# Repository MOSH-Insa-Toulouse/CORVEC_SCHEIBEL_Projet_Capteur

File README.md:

# CORVEC_SCHEIBEL_Projet_Capteur

[Lien GitHub du projet ](https://github.com/MOSH-Insa-Toulouse/CORVEC_SCHEIBEL_Projet_Capteur)

Étudiantes en 4ème année Génie Physique à l’INSA (Institut National des Sciences Appliquées) de Toulouse ce ReadMe présente le projet réalisé dans le cadre de l’UF « Du capteur au banc de test ». L’objectif de ce projet est de designer et construire un PCB Shield incluant un capteur de déformation en graphite couplé à un circuit analogique. Un code Arduino permet de contrôler le tout et de communiquer les mesures du capteur vers une application Android.

## Sommaire 

- [1. Contexte du projet](#1-contexte-du-projet)  

- [2. Fabrication du capteur](#2-fabrication-du-capteur)  
    - [a. Kicad](#a-kicad)
    - [b. Réalisation du PCB](#b-réalisation-du-pcb)
- [3. Contrôle et interface du capteur](#3-contrôle-et-interface-du-capteur)
- [a. Code Arduino](#a-code-arduino)
- [b. Application Android](#b-application-android)
- [4. Banc de test](#4-banc-de-test)
- [5. Pistes d'amélioration](#5-pistes-damélioration)
- [6. Commentaires et conclusion](#6-commentaires-et-conclusion)

## 1. Contexte du projet

Le crayon papier est un objet du quotidien et fait partie intégrante de nos vies depuis bien longtemps. La mine d’un crayon est composée d'une fine poudre de graphite liées par des argiles. Lorsque l’on effectue des traces de crayons sur une feuille de papier (surface naturellement poreuse), des particules ultrafines de graphite se déplosent en surface. Ces traces sont des films minces conducteurs constituées de réseaux percolés. Elles peuvent ainsi jouer le rôle de conducteur passif dans divers dispositifs et peuvent être également utilisées en tant que conducteur actif dans des capteurs piézorésistifs. En 2014, les chercheurs Cheng-Wei Lin, Zhibo Zhao, Jaemyung Kim & Jiaxing Huang ont publié l’article « Pencil Drawn Strain Gauges and Chemiresistors on Paper » dans lequel ils démontrent que « les traces de crayon peuvent fonctionner non seulement comme des jauges de contrainte pour détecter les déflexions de compression et de traction, mais également comme des résistances chimiques sensibles aux vapeurs chimiques volatiles »[1]. 

Pour rappels : Les crayons en graphite sont désignés comme ceci :

- 9H à H (avec H9 le plus dur et léger)
- HB
- 9B à B (avec 9B le plus doux et sombre)

Les résultats présentés par l’équipe de chercheurs sont les suivants : les résistances mesurées sans contrainte pour des mines 9B, 6B, 2B, and HB sont respectivement de 200 kΩ, 500 kΩ, 2MΩ, 20 MΩ. Plus les mines sont douces et sombres (donc contenant plus de graphite) plus la résistance est faible.  
L’étude des chercheurs a révélé que les traces laissées par des crayons de duretés supérieures et égales à 2H ne pouvaient être mesurées, elles étaient donc non conductrices. Cependant les traces de crayons HB ont montré la plus grande réponse, elles se situeraient à priori juste au-dessus du seuil de percolation. Les mesures ont été réalisés via un programme Labview avec un compteur source Keithley 2400 d’une valeur de 5760€.  

À travers ce projet nous avons cherché à mesurer la valeur de résistance 2H et ce, avec un dispositif bas coût et facilement transportable.

## 2. Fabrication du capteur

Le capteur de déformation en graphite est une jauge de contrainte. Le principe consiste ici appliquer des forces de compression ou de traction sur une feuille de papier où a été déposé du graphite via un crayon papier (Figure 1).  Comme énoncé précédemment, les traces laissées par le crayon vont, sous compression ou traction, présenter une variation de résistance. Suite à cette faible variation, on mesure une tension, grâce à un circuit d'amplification transimpédance.

Figure 1

### a. Kicad

La schématique du circuit a été créé via le logiciel LTSpice IV (Figures 2). La schématique présente une partie lecture analogique, nous utilisons un amplificateur trans-impédance. Il s’agit d’un convertisseur courant-tension permettant d’amplifier la sortie de courant du capteur.  Ce circuit trans-impédance à filtre passe-bas nous permet de récupérer les données du capteur de traction (pour plus de détails : voir notre datasheet, partie « Exemple d’intégration »). Une autre partie expose les modules pouvant être ajoutés sur la carte : un écran OLED, un Bluetooth et un encodeur rotatoire.  Après avoir généré la liste des empreintes des composants, nous avons pu concevoir notre PCB Shield grâce au logiciel KICAD (Figures 3).

Figures 2

Figures 3

### b. Réalisation du PCB

Le masque de notre PCB a ensuite été imprimé et placé sur une plaque recouverte d’une résine. La résine non protégée par le masque est exposée aux UV. Une solution basique attaque les dépôts de résine insolée pour révéler certaines zones du PCB. La plaque est ensuite chauffée dans une solution afin d'attaquer les zones de cuivre non désirées. Le PCB est ensuite percé et les différents composants y sont soudés (Figures 4).

Figures 4

## 3. Contrôle et interface du capteur

### a. Code Arduino

Le PCB se plug sur une carte Arduino (Figure 5). Le branchement est détaillé dans la datasheet. Le code Arduino ([lien code](/Arduino_code/Arduino_capteur_graphite.ino)) permet de :

- Lire la tension (ADC) délivrée par le capteur (capteur graphite + circuit amplificateur)
- D'envoyer la donnée vers l'application Android via la connection Blueotooth établie
- De calculer la resistance du capteur graphite équivalente à cette tension pour l'afficher sur l'écran OLED

Figure 5

### b. Application Android

L'application Android affiche la valeur de la tension lue par l'ensemble du capteur. Elle calcule la valeur de la résistance en (Ohm) et l'affiche au dessus de la tension. Parallèlement un graphique montre la valeur de la résistance en fonction du temps.
L'îcone "Bluetooth" permet d'ouvrir la liste des appareils associés au smartphone pour établir la connexion Bluetooth avec le capteur.

Cette application a été créée sur le site [MIT app inventor](https://appinventor.mit.edu/). Pour télécharger notre application, il faut ouvrir cette [apk](/Application_Android/Capteur.apk) depuis un smartphone.

## 4. Banc de test

Une fois le branchement du capteur effectué nous réalisons les mesures de caractérisation. Nous utilisons une pièce imprimée en 3D(Figure 6). Elle comporte 7 rayons différents, cela permet d’appliquer plusieurs contraintes connues à notre capteur. Pour nos mesures les diamètres notés R1 à R6 sont utilisés.

- ETAPE 1 : Dépôt du graphite à tester sur la feuille de papier, en coloriant.
- ETAPE 2 : Lecture de la valeur de l’offset, notée R0 grâce à l’écran OLED ou via l’application.
- ETAPE 3 : Application de la première contrainte au rayon R1 et lecture de la résistance R du capteur.
- ETAPE 4 : Calcul de ∆R.
- ETAPE 5 : Répétition des étapes 2, 3 et 4 jusqu’au rayon R6.
- ETAPE 6 : Calcul de la déformation appliquée pour chaque rayon.
- ETAPE 7 : Affichage de (∆R )/R en fonction de la déformation.

Figure 6

## 5. Pistes d'améliorations

Les différentes mesures effectuées ne sont pas répétables. Dès la première mesure du protocole de test, le capteur entre dans le domaine de non-détérioration, c’est-à-dire que ses caractéristiques métrologiques sont modifiées. En effet la résistance d'offset varie après chaque nouvelle contrainte appliquée, ce qui influe sur le résultat, d’où l’importance de relever avant chaque mesure la nouvelle valeur de R0. À partir des rayons R3 ou R4 nous entrons dans le domaine de non-destruction du capteur, les caractéristiques métrologiques sont modifiées de façon irréversible. L’offset devient de plus en plus important et il n’est plus possible de répéter les précédentes mesures sans entacher les résultats d’erreurs. Il est plutôt conseillé de changer de capteur, en effet lorsqu’une contrainte trop élevée est appliquée, les réseaux percolés sur graphite ne peuvent revenir à leur état d’origine.

Plusieurs pistes d’améliorations sont envisageables, sur différents éléments du capteur :

**Concernant la précision des mesures** du banc de test : les mesures effectuées sont peu répétables. En effet, entre chaque série de mesures les déformations appliquées peuvent varier (le banc de test ne permettant pas d’appliquer une déformation identique) tout comme la  concentration de graphite déposée sur le papier (manque de précision du coloriage).

Pour diminuer l’erreur sur les mesures, nous pourrions répéter les tests sur un grand nombre de capteurs équivalents et pour chaque contrainte, nous aurions ainsi une moyenne arithmétique de la valeur de résistance.

Un autre moyen d’améliorer la répétabilité des mesures, serait de fabriquer un banc de test plus précis et fiable, par exemple l’utilisation d’un banc de test contrôlé par un cervo moteur permettrait d’appliquer une contrainte beaucoup plus précise et répétable que la contrainte appliquée à la main sur la pièce 3D.

Concernant le **PCB** : Pour adapter les mesures des résistances en fonction des types de capteur (donc en fonction des différents types de graphite), il serait très utile de pouvoir modifier le gain de l’amplificateur transimpédance. Le gain est influencé par le rapport R2/R3, R3 est important pour le filtrage, c’est donc la résistance R2 qui permet de jouer sur le gain. Plutôt que de souder une résistance d’une valeur fixe, il serait alors judicieux de souder des plots. Ainsi le changement de R2 serait plus facile.

Enfin le **code Arduino** pourrait également être développé. Si des plots sont soudés sur le PCB pour pouvoir changer la résistance R2, alors l’Arduino pourrait gérer un encodeur rotatoire. Celui-ci permettrait de modifier la valeur de R2 dans le code, et ainsi faire le lien entre la résistance physique et la valeur de R2 dans les formules du code. Le code Arduino peut toujours être amélioré, d’autres fonctionnalités sont possibles, comme par exemple l’affichage d’un menu sur l’écran OLED. Ce menu permettrait d’entrer une nouvelle valeur de R2, de modifier la valeur de l’offset du capteur ou encore de changer la vitesse de transfert des données entre le capteur et l’application, etc…

## 6. Commentaires et conclusion

Les résultats des mesures effectuées sont disponibles dans notre datasheet. Nous pouvons apporter les commentaires suivants : plus une mine est douce, plus elle est concentrée en carbone et moins la variation de résistance est importante. En effet les réseaux percolés sont beaucoup plus denses et on a une meilleure conduction. Lorsqu’on applique une contrainte sur ce type de mine, les réseaux percolés, du fait de leur nombre, sont peu impactés. Ce qui pourrait expliquer pourquoi la mine la plus concentrée 6B a montré une variation de résistance quasiment constante. Les graphites 3B et B varient le plus linéairement. L'application d'une traction vient déconnecter les réseaux, on a une diminution de la conductivité. Les mines plus dures comme HB ou 2H creusent davantage le papier mais sont moins concentrées en carbone. Les mesures effectuées présentaient de très fortes variations de résistances et ces dernières étaient très instables, donc plus difficile à mesurer notamment le 2H. Cependant, malgré les grandes incertitudes sur ces mesures nous avons tout de même observé des variations de résistance sur le 2H contrairement aux chercheurs cités précédemment. Donc, la concentration en graphite du type 2H se situe probablement au-dessus du seuil de percolation.

Il est surprenant de réaliser un capteur de déformation avec si peu de matériel, une simple feuille de papier coloriée au crayon permet de mettre en évidence de faibles déformations. Cependant on notera que le capteur en graphite est très peu précis et relativement fragile, sans oublier qu’il manque fortement de répétabilité. Cet inconvénient est problématique pour un capteur, car il ne permet pas d'accéder de manière fiable à des valeurs de contraintes inconnues.
L’élaboration de ce capteur en graphite a permis de nous rendre compte de l’importance de certaines caractéristiques des capteurs. Ce projet nous a aussi fait découvrir l’Arduino, qui est très pratique par sa polyvalence et ses multiples applications.

Références :

[1] Lin, C.-W., Zhao, Z., Kim, J. & Huang, J. Pencil Drawn Strain
Gauges and Chemiresistors on Paper. Sci. Rep. 4, 3812; DOI:10.1038/srep03812 (2014)

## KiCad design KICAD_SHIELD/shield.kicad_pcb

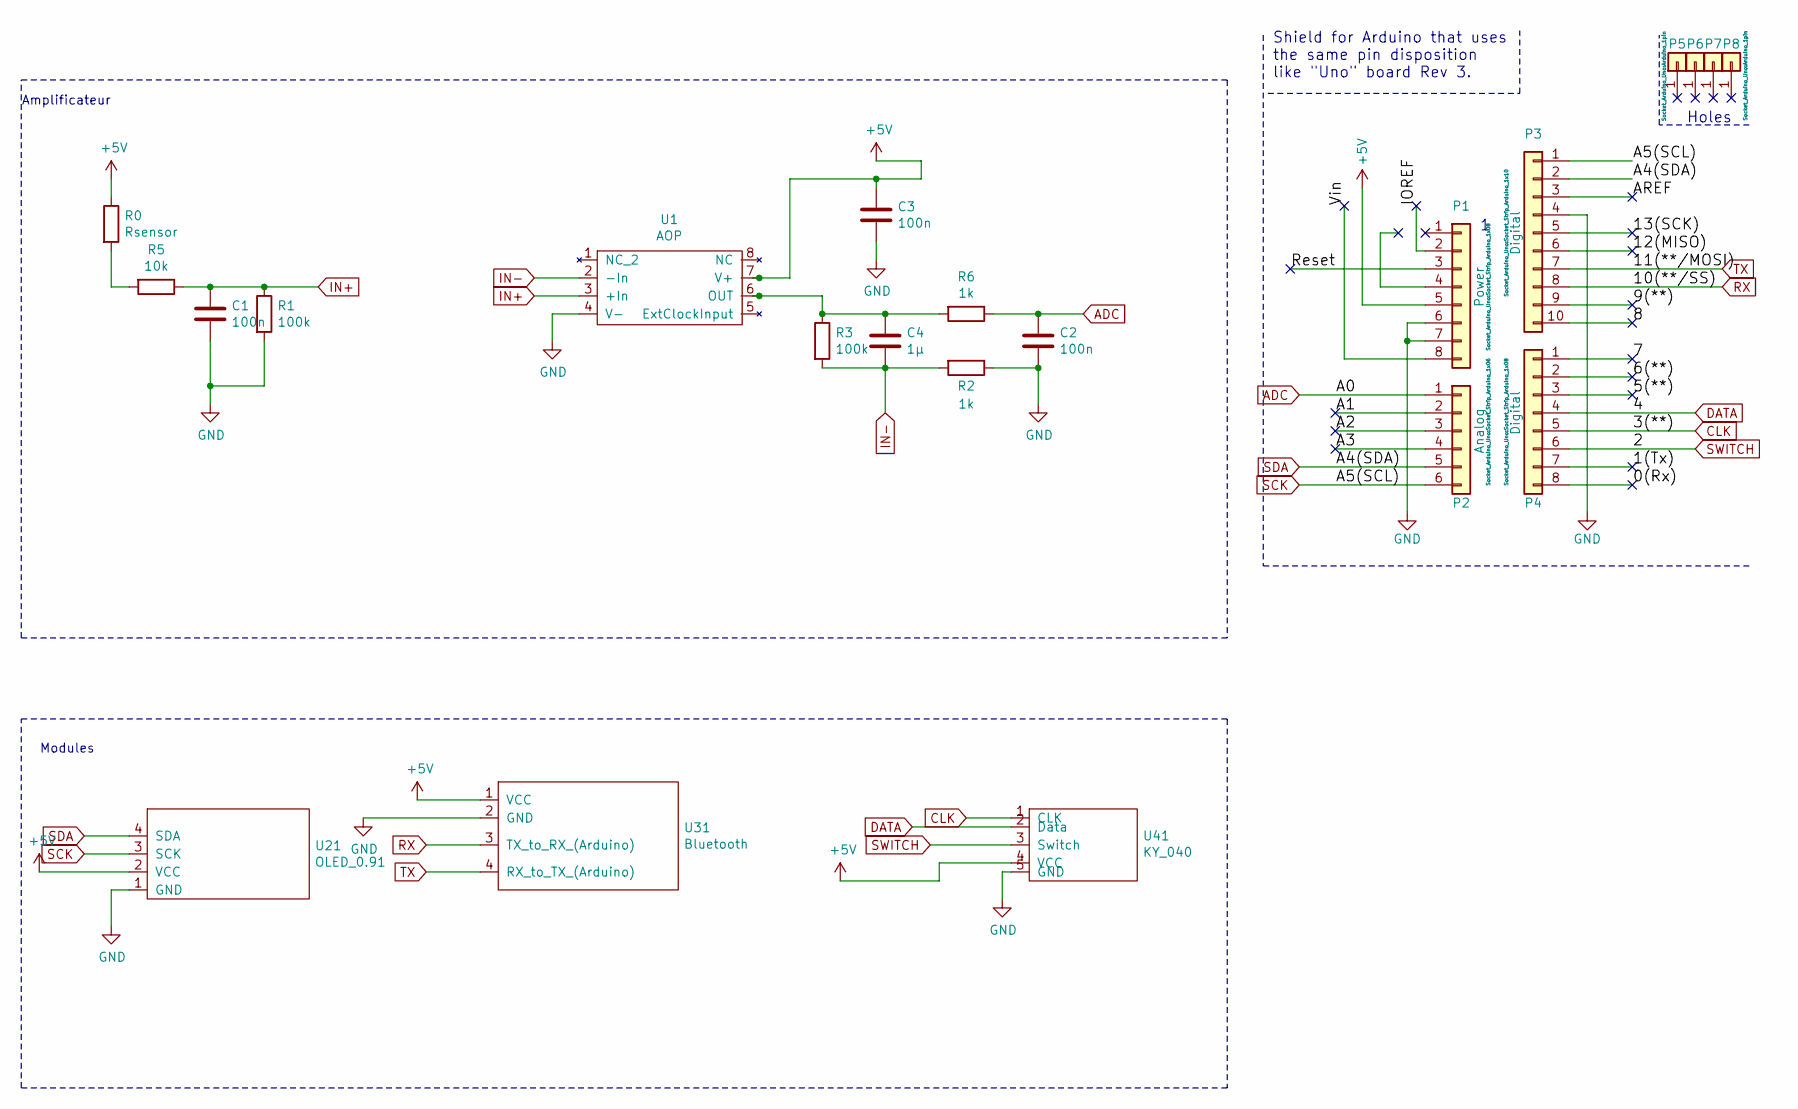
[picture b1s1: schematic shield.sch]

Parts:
C1, C2, C3: 100n; C_Axial_L5.1mm_D3.1mm_P7.50mm_Horizontal
C4: 1µ; C_Rect_L7.2mm_W11.0mm_P5.00mm_FKS2_FKP2_MKS2_MKP2
P1: Power; Socket_Strip_Arduino_1x08
P2: Analog; Socket_Strip_Arduino_1x06
P3: Digital; Socket_Strip_Arduino_1x10
P4: Digital; Socket_Strip_Arduino_1x08
P5, P6, P7, P8: CONN_01X01; Arduino_1pin
R0: Rsensor
R1, R3: 100k; R_Axial_DIN0207_L6.3mm_D2.5mm_P10.16mm_Horizontal
R2, R6: 1k; R_Axial_DIN0207_L6.3mm_D2.5mm_P10.16mm_Horizontal
R5: 10k; R_Axial_DIN0207_L6.3mm_D2.5mm_P10.16mm_Horizontal
U1: AOP
U21: OLED_0.91; OLED
U31: Bluetooth; BluetoothU3
U41: KY_040; Encodeur

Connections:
+5V: C3.1, P1.5, R0.1, U1.7 (V+), U21.2 (VCC), U31.1 (VCC), U41.4 (VCC)
/0(Rx): P4.8
/1(Tx): P4.7
/5(**): P4.3
/6(**): P4.2
/7: P4.1
/8: P3.10
/9(**): P3.9
/12(MISO): P3.6
/13(SCK): P3.5
/A1: P2.2
/A2: P2.3
/A3: P2.4
/AREF: P3.3
/IOREF: P1.2
/Reset: P1.3
/Vin: P1.8
ADC: C2.1, P2.1, R6.1
CLK: P4.5, U41.1 (CLK)
DATA: P4.4, U41.2 (Data)
GND: C1.2, C2.2, C3.2, P1.6, P1.7, P3.4, R1.2, R2.1, U1.4 (V-), U21.1 (GND), U31.2 (GND), U41.5 (GND)
IN+: C1.1, R1.1, R5.1, U1.3 (+In)
IN-: C4.2, R2.2, R3.2, U1.2 (-In)
unnamed: C4.1, R3.1, R6.2, U1.6 (OUT)
unnamed: R0.2, R5.2
RX: P3.8, U31.3 (TX_to_RX_(Arduino))
SCK: P2.6, P3.1, U21.3 (SCK)
SDA: P2.5, P3.2, U21.4 (SDA)
SWITCH: P4.6, U41.3 (Switch)
TX: P3.7, U31.4 (RX_to_TX_(Arduino))

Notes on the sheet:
Holes
Shield for Arduino that uses the same pin disposition like "Uno" board Rev 3.
Amplificateur
Modules

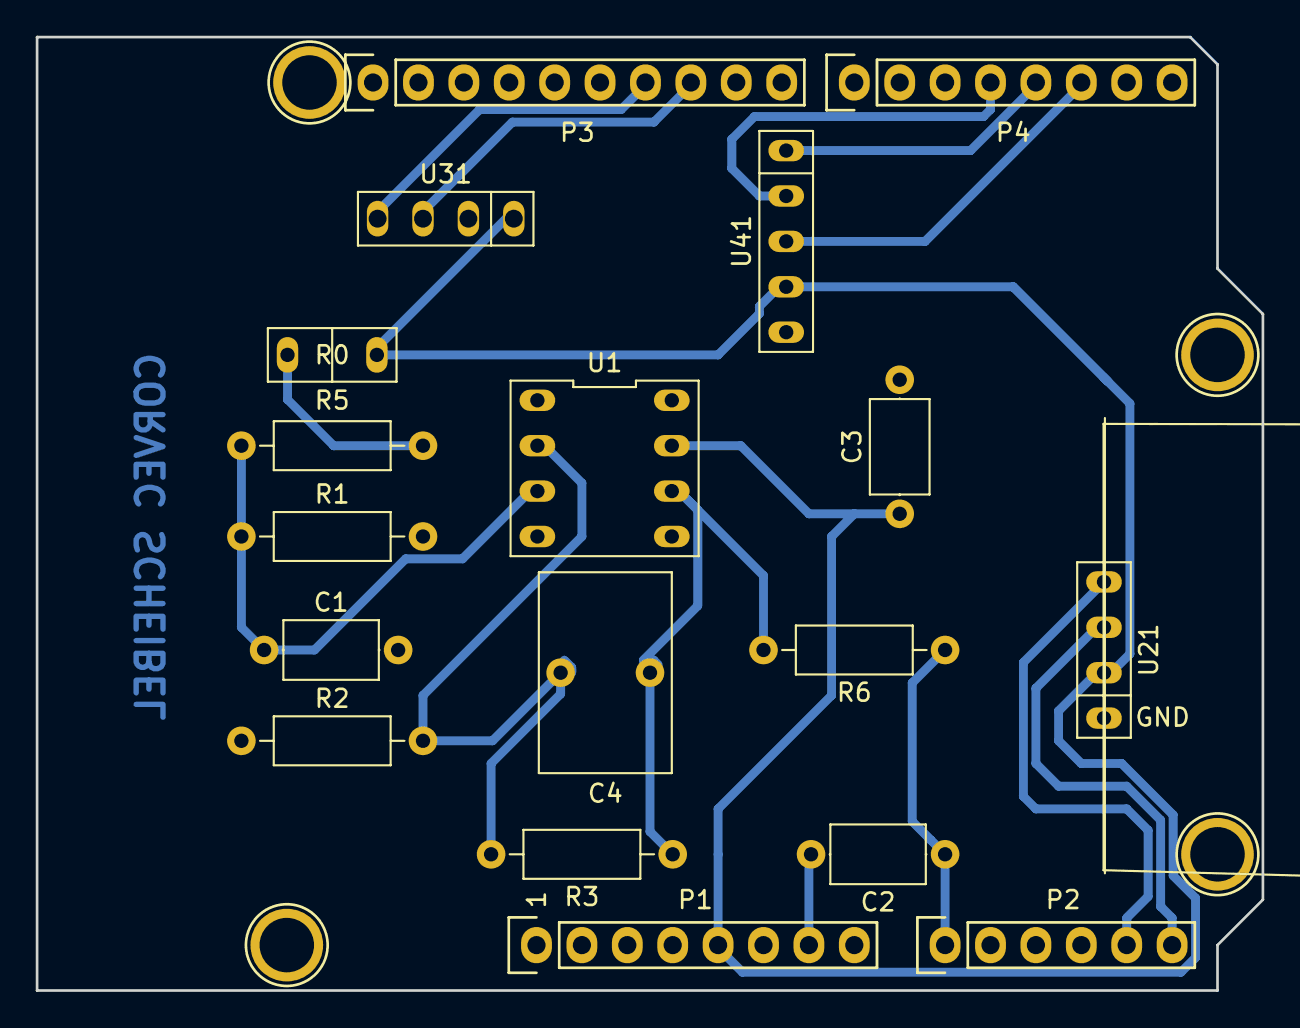
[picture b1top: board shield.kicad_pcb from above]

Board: 2 copper layers, 68.6 x 53.3 mm, 22 parts (0 on the bottom side), 14 nets.

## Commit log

2021-03-17 import folders
2021-05-03 up_date2
2021-05-03 update3
2021-05-04 update4
2021-05-10 update5
